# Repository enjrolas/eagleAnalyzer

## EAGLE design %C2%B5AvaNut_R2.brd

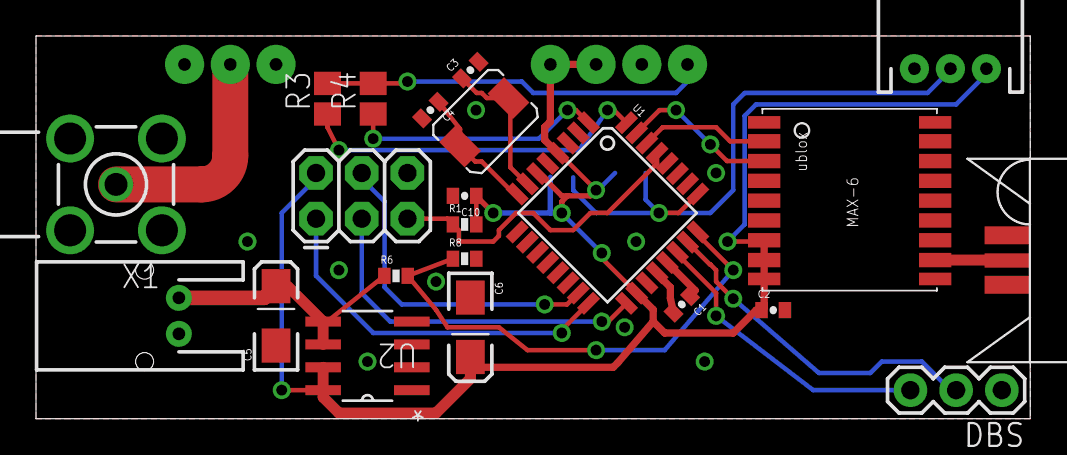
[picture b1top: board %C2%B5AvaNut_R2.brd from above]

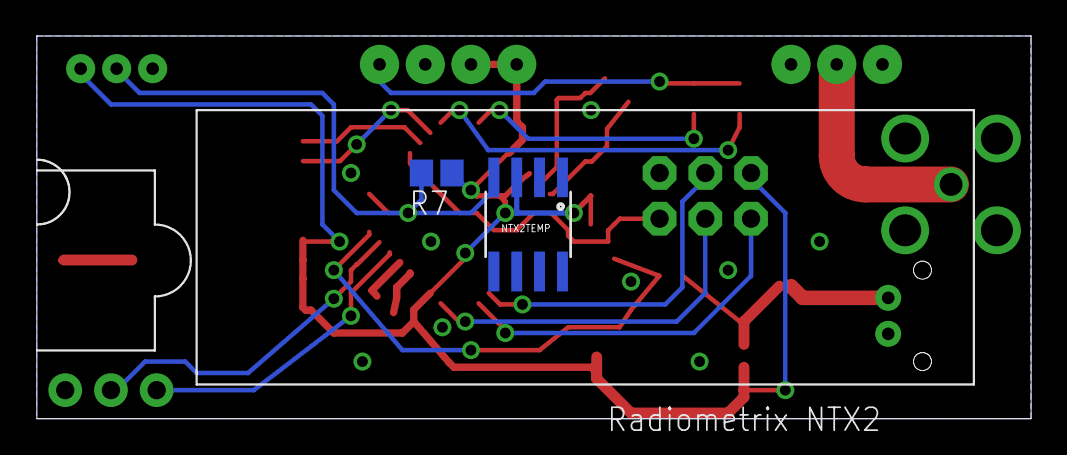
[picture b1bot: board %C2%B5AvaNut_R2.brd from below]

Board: 2 copper layers, 55.2 x 21.3 mm, 25 parts (3 on the bottom side), 21 nets.

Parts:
C1, C2, C10: 0.1uF; 0402-CAP
C3, C4: 18pF; 0402-CAP
C5: EIA3216-KIT
C6: 4.7uF; EIA3216-KIT
DBS: 1X03
FUCKINGANNOYING: AVR_SPI_PRG_6PTH; 2X3
JP6: JST-3-PTH
NTX2TEMP: DS1821; DS18B20_SOIC
R1, R8: 10k; 0402-RES
R3: 47K; R0805
R4: 39k; R0805
R6: 100k; 0402-RES
R7: 4k7; R0805
U1: ATMEGA328; TQFP32-08
U2: TPS76633D; SOIC127P600X175-8N
U$1: UBLOX_MAX-6
U$2: ABRACON_ABM3_CRYSTAL
U$3: SARANTEL-SR1202
U$4: NTX2
U$6: M02-JST-PTH
X1: BU-SMA-H

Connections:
AREF: C1.2, U1.20
GND: C1.1, C2.2, C3.2, C4.2, C5.C, C6.C, C10.2, DBS.1, FUCKINGANNOYING.6, JP6.1, NTX2TEMP.GND, R8.2, U1.3, U1.5, U1.21, U2.3, U2.4, U$1.1_GND, U$1.6_V_BCKP, U$1.10_GND, U$1.12_GND, U$3.GND1, U$3.GND2, U$4.0V, U$4.RFGND, U$4.RFGND2, U$6.1, X1.2, X1.3, X1.4, X1.5
MISO: FUCKINGANNOYING.1, U1.16
MOSI: FUCKINGANNOYING.4, U1.15
unnamed: U$4.RFOUT, X1.1
unnamed: R3.2, R4.2, U$4.TXD
unnamed: U$1.11_RF_IN, U$3.FEED
unnamed: C3.1, U1.7, U$2.P$2
unnamed: C4.1, U1.8, U$2.P$1
NSS_RX: DBS.2, U1.23
NSS_TX: DBS.3, U1.22
RADIO_MARK: R3.1, U1.32
RADIO_SPACE: R4.1, U1.1
RESET: FUCKINGANNOYING.5, R1.1, U1.29
SCK: FUCKINGANNOYING.3, U1.17
TEMPSENSORS: JP6.2, NTX2TEMP.DQ, R7.2, U1.25
UBLOX_RXD: U1.31, U$1.3_RXD1
UBLOX_TXD: U1.30, U$1.2_TXD1
VBATT: C5.A, R6.1, U2.5, U2.6, U$6.2
VBATTADC: R6.2, R8.1, U1.24
VCC: C2.1, C6.A, C10.1, FUCKINGANNOYING.2, JP6.3, NTX2TEMP.VCC, R1.2, R7.1, U1.4, U1.6, U1.18, U2.7, U2.8, U$1.7_VCC_IO, U$1.8_VCC, U$1.9_V_RESET, U$4.EN, U$4.VCC

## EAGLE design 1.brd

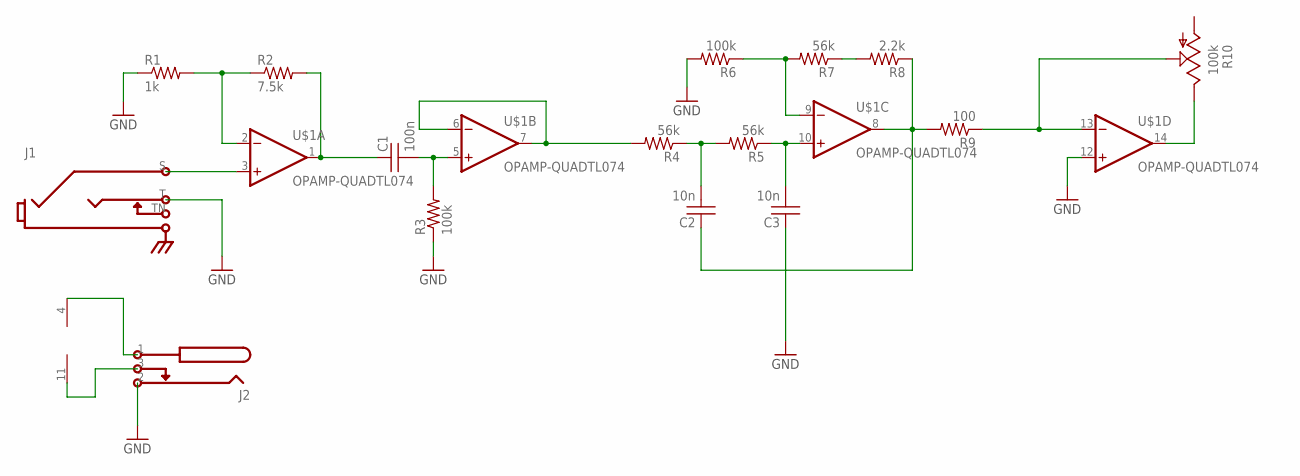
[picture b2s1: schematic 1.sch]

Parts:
C1: 100n; BOX-2.5MM-7.2MM
C2, C3: 10n; BOX-2.5MM-7.2MM
J1: MONOSW1GND; NEUTRIK-NRJ4HM-1
J2: BOSS-SWITCHING; KOBICONN-163-5010-E
R1: 1k; 0.25W-0.4IN-CARBONCOMP
R2: 7.5k; 0.25W-0.4IN-CARBONCOMP
R3, R6: 100k; 0.25W-0.4IN-CARBONCOMP
R4, R5, R7: 56k; 0.25W-0.4IN-CARBONCOMP
R8: 2.2k; 0.25W-0.4IN-CARBONCOMP
R9: 100; 0.25W-0.4IN-CARBONCOMP
R10: 100k; POT-SIDE-16MM-BITECH-P160KN
U$1: OPAMP-QUADTL074; DIP14

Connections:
0: C3.P$1 (1), J1.T, J2.2 (VCC), R1.1, R3.1, R6.2, U$1.12 (IN+)
unnamed: R1.2, R2.1, U$1.2 (IN-)
unnamed: C1.P$1 (1), R2.2, U$1.1 (OUT)
unnamed: C1.P$2 (2), R3.2, U$1.5 (IN+)
unnamed: R4.2, U$1.6 (IN-), U$1.7 (OUT)
unnamed: C2.P$2 (2), R4.1, R5.2
unnamed: C3.P$2 (2), R5.1, U$1.10 (IN+)
unnamed: R10.P$3 (3), U$1.14 (OUT)
unnamed: R6.1, R7.2, U$1.9 (IN-)
unnamed: R7.1, R8.2
unnamed: J1.S, U$1.3 (IN+)
unnamed: R9.1, R10.P$2 (2), U$1.13 (IN-)
unnamed: J2.1 (GND), U$1.4 (VCC)
unnamed: J2.3 (SW), U$1.11 (VEE)
unnamed: C2.P$1 (1), R8.1, R9.2, U$1.8 (OUT)

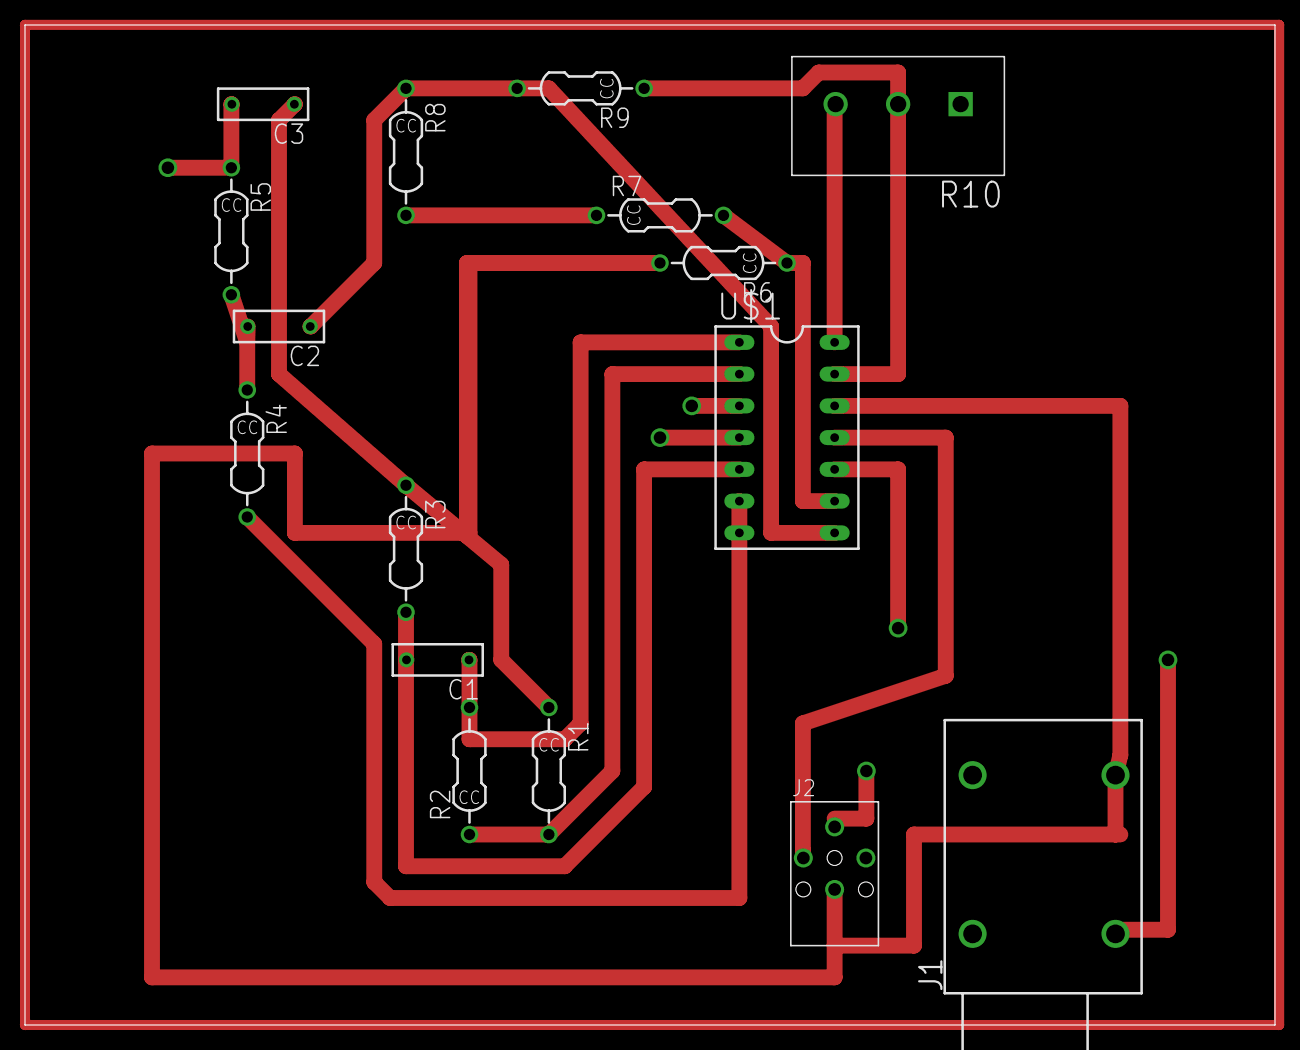
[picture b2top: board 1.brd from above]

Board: 2 copper layers, 100.0 x 80.0 mm, 16 parts (0 on the bottom side), 15 nets.

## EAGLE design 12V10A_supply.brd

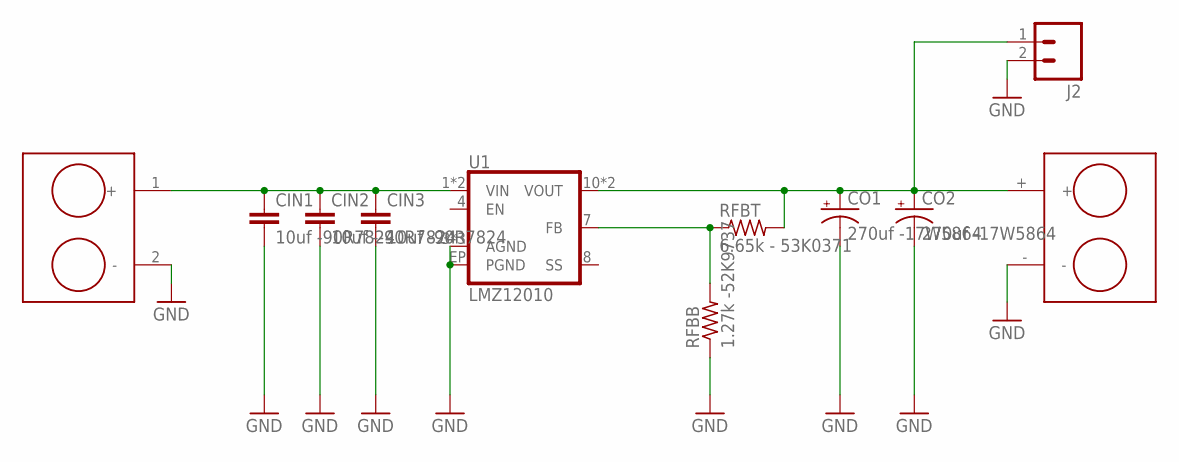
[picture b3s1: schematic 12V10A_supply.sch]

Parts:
CIN1, CIN3: 10uf -90R7824; C1210
CIN2: 10uf --90R7824; C1210
CO1, CO2: 270uf -17W5864; JC0CAP
J1: 5569-02A2MS-225; 0050362375
J2: M02PTH; 1X02
J3: MC24356; 2PINTERMINAL
RFBB: 1.27k -52K9737; M0805
RFBT: 6.65k - 53K0371; M0805
U1: LMZ12010; TO-PMOD-11

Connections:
GND: CIN1.2, CIN2.2, CIN3.2, CO1.-, CO2.-, J1.2 (-), J2.2, J3.-, RFBB.1, U1.3 (AGND), U1.5 (AGND), U1.6 (AGND), U1.EP (PGND)
unnamed: RFBB.2, RFBT.1, U1.7 (FB)
VIN: CIN1.1, CIN2.1, CIN3.1, J1.1 (+), U1.1 (VIN), U1.2 (VIN)
VOUT: CO1.+, CO2.+, J2.1, J3.+, RFBT.2, U1.10 (VOUT), U1.11 (VOUT)

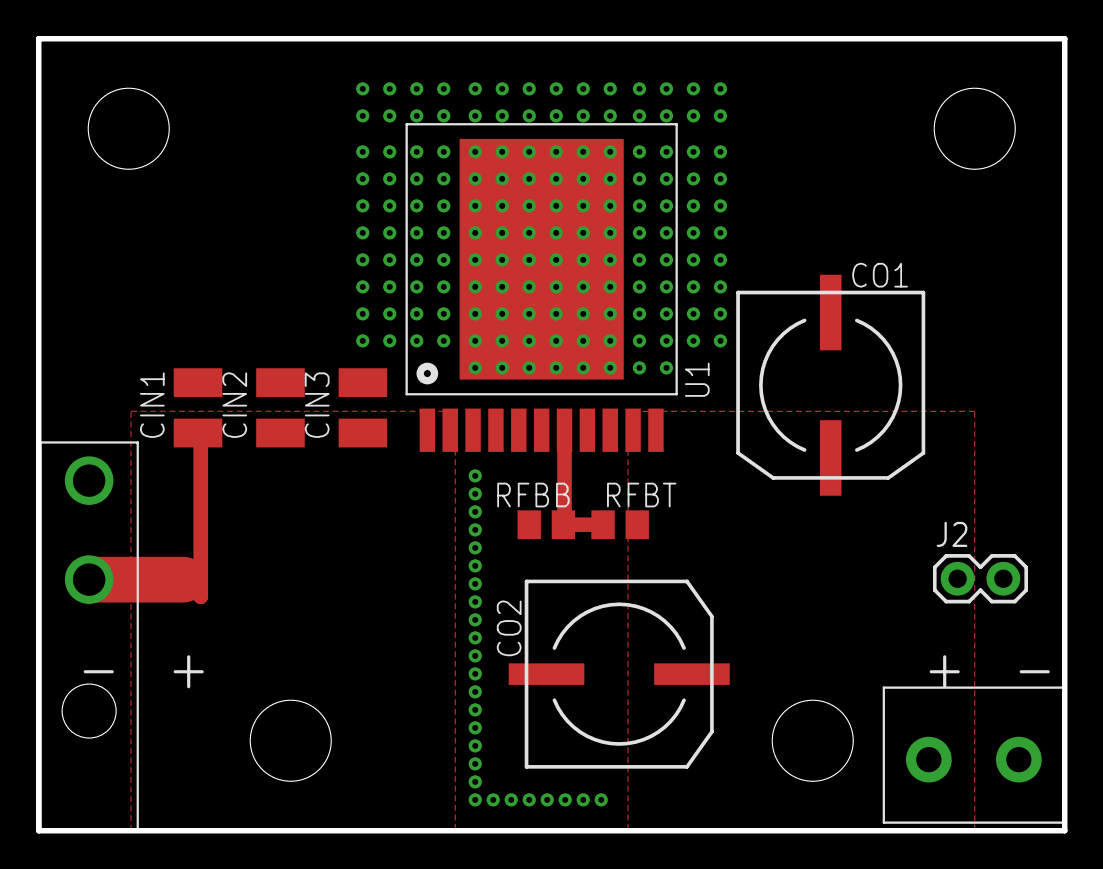
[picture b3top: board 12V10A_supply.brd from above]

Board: 2 copper layers, 57.0 x 44.0 mm, 11 parts (0 on the bottom side), 4 nets.

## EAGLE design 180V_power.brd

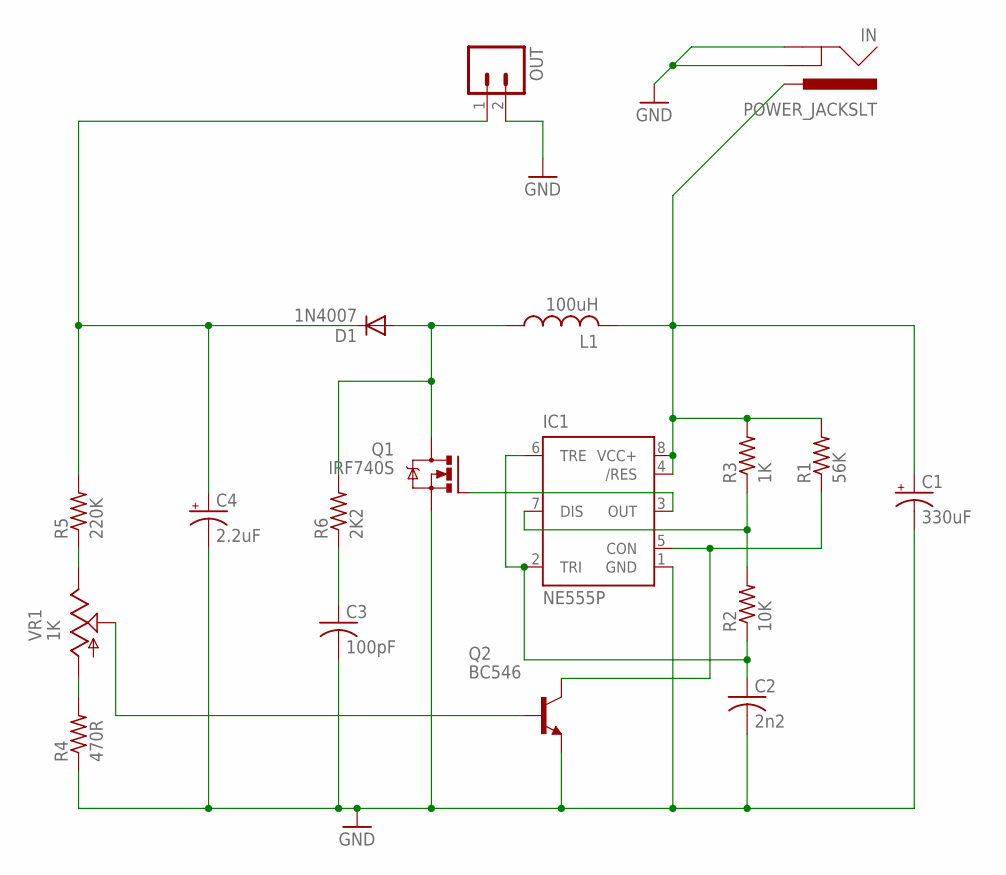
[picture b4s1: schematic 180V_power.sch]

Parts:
C1: 330uF; E5-10,5
C2: 2n2; C1206K
C3: 100pF; C1206K
C4: 2.2uF; E3,5-8
D1: 1N4007; SMA-DIODE
IC1: NE555P; DIL08
IN: POWER_JACKSLT; POWER_JACK_SLOT
L1: 100uH; TFI0307
OUT: M023.5MM; SCREWTERMINAL-3.5MM-2
Q1: IRF740S; TO263
Q2: BC546; TO92-EBC
R1: 56K; R1206
R2: 10K; R1206
R3: 1K; R1206
R4: 470R; 0207/10
R5: 220K; 0207/10
R6: 2K2; R1206
VR1: 1K; CA6V

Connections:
GND: C1.-, C2.2, C3.2, C4.-, IC1.1 (GND), IN.GND@1 (GNDBREAK), IN.GND@2 (GND), OUT.2, Q1.2 (S), Q2.E, R4.1
unnamed: IC1.3 (OUT), Q1.1 (G)
unnamed: C3.1, R6.1
unnamed: IC1.5 (CON), Q2.C, R1.1
unnamed: IC1.7 (DIS), R2.2, R3.1
unnamed: C2.1, IC1.2 (TRI), IC1.6 (TRE), R2.1
unnamed: D1.A, L1.1, Q1.3 (D), R6.2
unnamed: C4.+, D1.C, OUT.1, R5.2
unnamed: R5.1, VR1.E
unnamed: R4.2, VR1.A
unnamed: Q2.B, VR1.S
unnamed: C1.+, IC1.4 (/RES), IC1.8 (VCC+), IN.PWR, L1.2, R1.2, R3.2

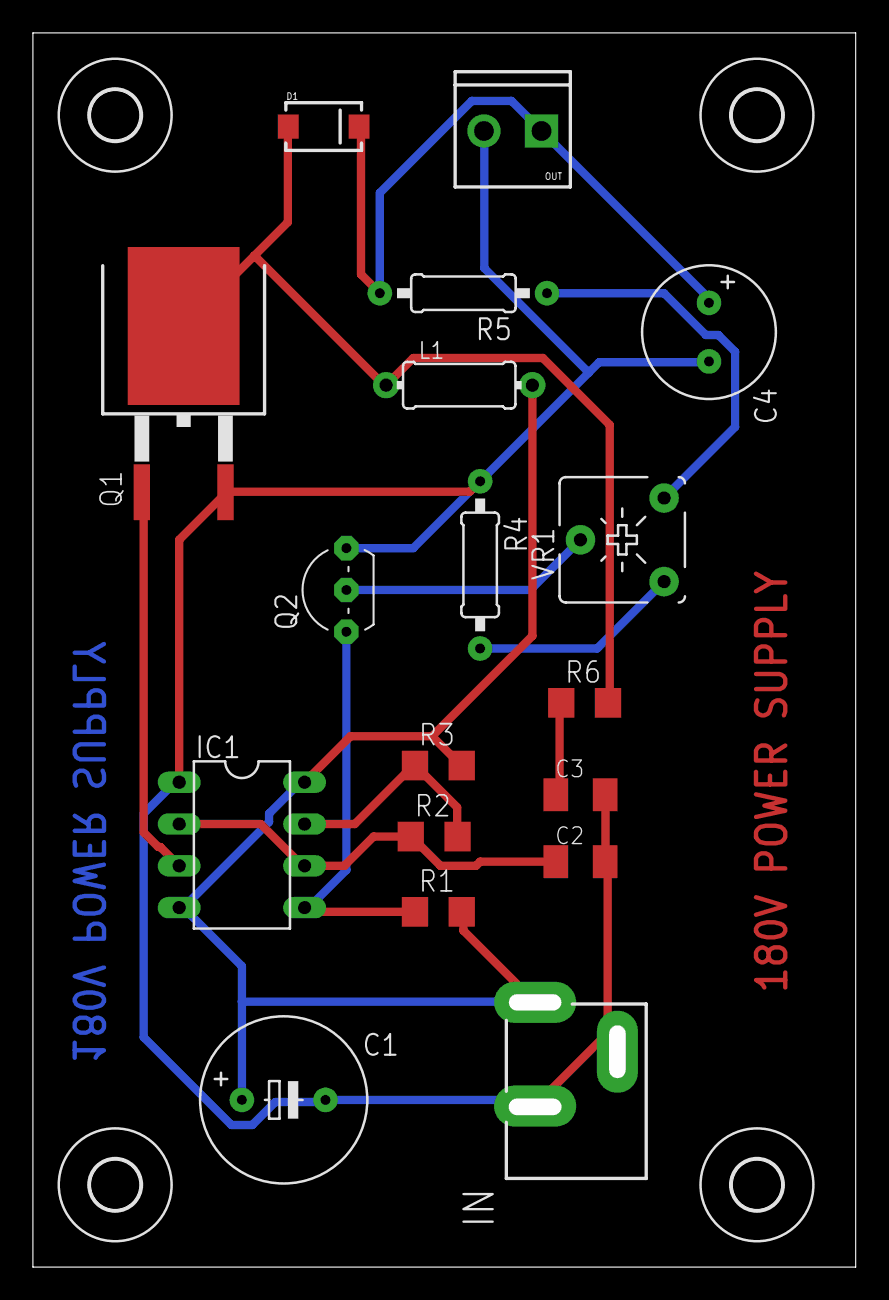
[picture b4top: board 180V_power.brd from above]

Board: 2 copper layers, 50.0 x 75.0 mm, 22 parts (0 on the bottom side), 12 nets.

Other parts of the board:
U$1, U$2, U$3, U$4: 3,0

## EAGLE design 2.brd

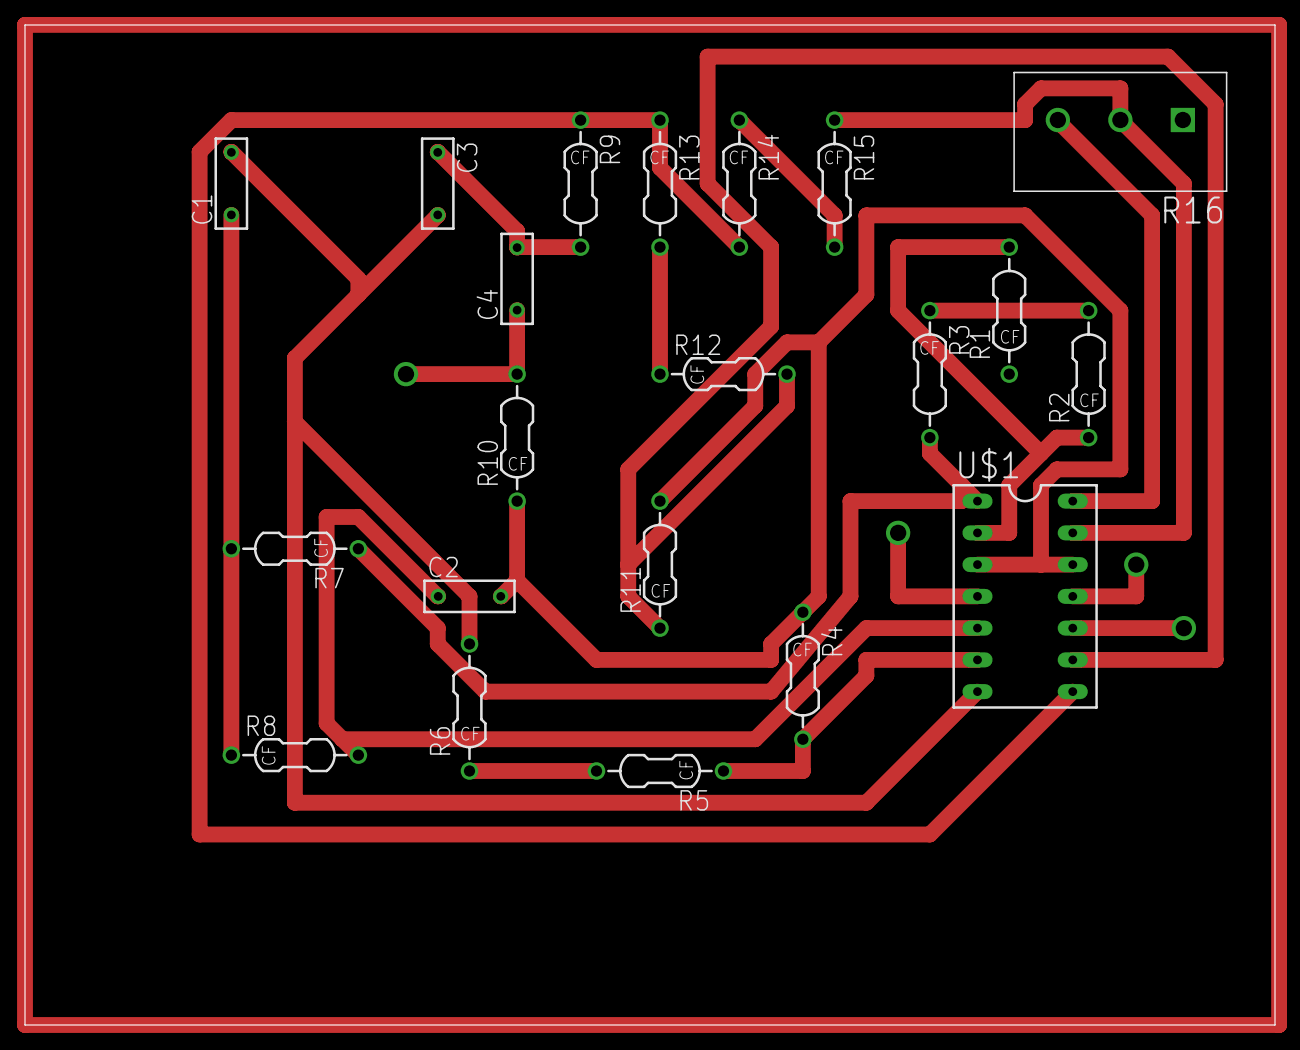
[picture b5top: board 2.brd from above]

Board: 2 copper layers, 100.0 x 80.0 mm, 21 parts (0 on the bottom side), 17 nets.

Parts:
C1, C2, C3, C4: 10n; BOX-2.5MM-7.2MM
R1, R4, R11, R15: 100k; 0.25W-0.4IN-CARBONFILM
R2, R5, R9, R10, R12: 56k; 0.25W-0.4IN-CARBONFILM
R3: 6.8k; 0.25W-0.4IN-CARBONFILM
R6, R13: 2.2k; 0.25W-0.4IN-CARBONFILM
R7, R8: 5.6k; 0.25W-0.4IN-CARBONFILM
R14: 100; 0.25W-0.4IN-CARBONFILM
R16: 100k; POT-SIDE-16MM-BITECH-P160KN
U$1: OPAMP-QUADTL074; DIP14

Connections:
0: C2.P$2, R4.1, R10.1, R11.2, U$1.3, U$1.12
unnamed: R1.2, R2.1, U$1.2
unnamed: R2.2, R3.1
unnamed: R3.2, R7.1, U$1.1
unnamed: C1.P$1, R7.2, R8.1
unnamed: C2.P$1, R8.2, U$1.5
unnamed: R4.2, R5.1, U$1.6
unnamed: R5.2, R6.1
unnamed: R16.P$3, U$1.14
unnamed: C3.P$1, C4.P$2, R9.2
unnamed: R11.1, R12.2, U$1.9
unnamed: R12.1, R13.2
unnamed: C4.P$1, R10.2, U$1.10
unnamed: R14.1, R15.2
unnamed: R15.1, R16.P$2, U$1.13
unnamed: C1.P$2, C3.P$2, R6.2, U$1.7
unnamed: R9.1, R13.1, R14.2, U$1.8

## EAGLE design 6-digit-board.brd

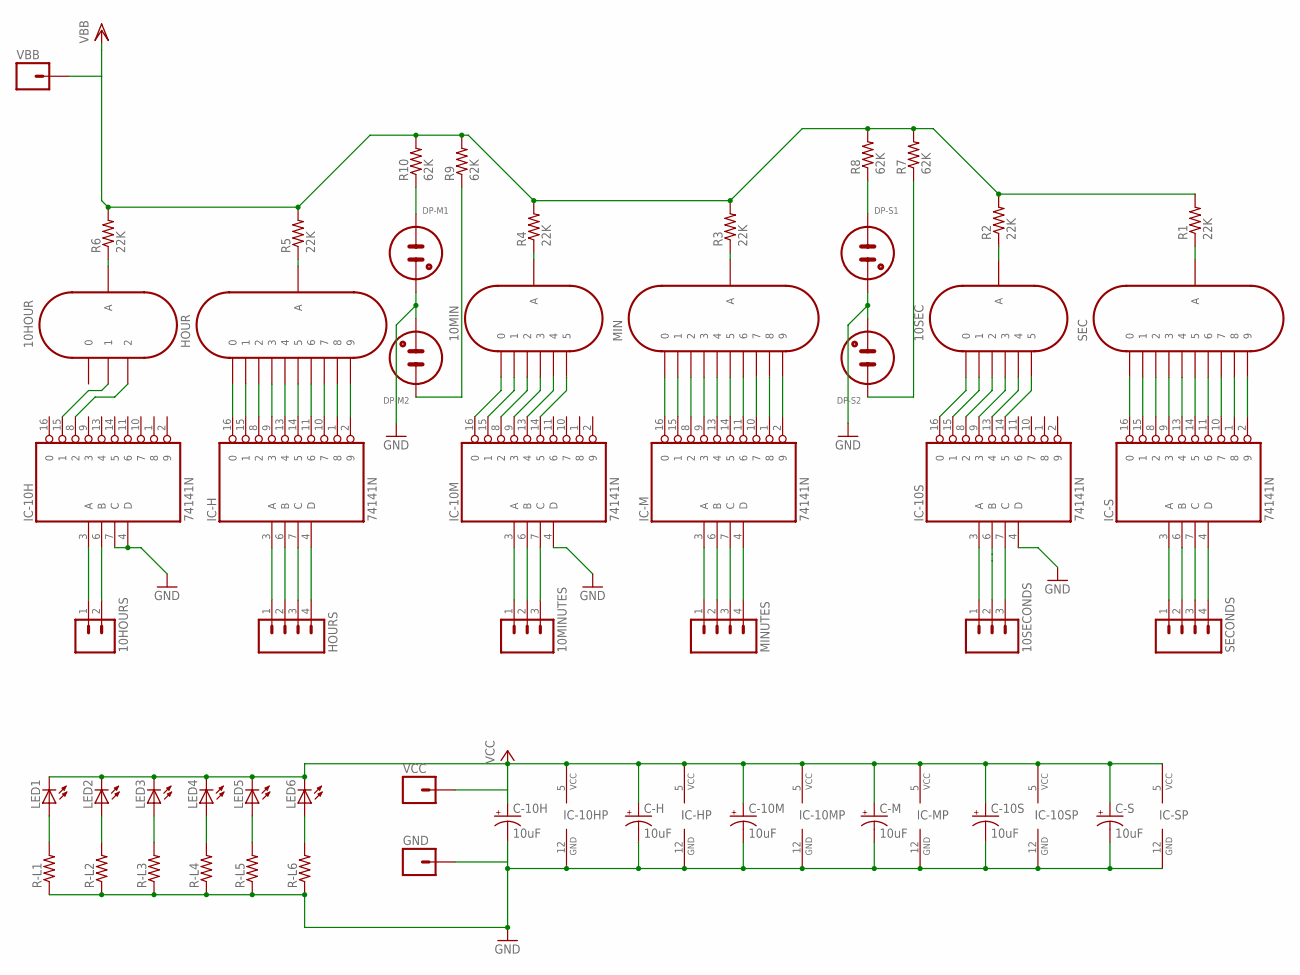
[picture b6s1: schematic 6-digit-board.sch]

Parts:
10HOUR: IN-12_2DIGIT
10HOURS: M02PTH3; 1X02_LONGPADS
10MIN, 10SEC: IN-12_6DIGIT
10MINUTES, 10SECONDS: M03LONGPADS; 1X03_LONGPADS
C-10H, C-10M, C-10S: 10uF; B/3528-21R
C-H: 10uF; B/3528-21R
C-M: 10uF; B/3528-21R
C-S: 10uF; B/3528-21R
DP-M1, DP-M2: INS-1
DP-S1, DP-S2: INS-1
GND: M01PTH; 1X01
HOUR: IN-12A-NO_DP; IN-12_NO-DP
HOURS: M04LONGPADS; 1X04_LONGPADS
IC-10H, IC-10M, IC-10S: 74141N; DIL16
IC-H: 74141N; DIL16
IC-M: 74141N; DIL16
IC-S: 74141N; DIL16
LED1, LED2, LED3, LED4, LED5, LED6: LED1210
MIN: IN-12A-NO_DP; IN-12_NO-DP
MINUTES: M04LONGPADS; 1X04_LONGPADS
R1, R2, R3, R4, R5, R6: 22K; 0207/10
R7, R8, R9, R10: 62K; 0207/10
R-L1, R-L2, R-L3, R-L4, R-L5, R-L6: RESISTORR1206; R1206
SEC: IN-12A-NO_DP; IN-12_NO-DP
SECONDS: M04LONGPADS; 1X04_LONGPADS
VBB: M01PTH; 1X01
VCC: M01PTH; 1X01

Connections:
GND: C-10H.-, C-10M.-, C-10S.-, C-H.-, C-M.-, C-S.-, DP-M1.K, DP-M2.K, DP-S1.K, DP-S2.K, GND.1, IC-10H.4 (D), IC-10H.7 (C), IC-10H.12 (GND), IC-10M.4 (D), IC-10M.12 (GND), IC-10S.4 (D), IC-10S.12 (GND), IC-H.12 (GND), IC-M.12 (GND), IC-S.12 (GND), R-L1.1, R-L2.1, R-L3.1, R-L4.1, R-L5.1, R-L6.1
unnamed: 10HOUR.A, R6.1
unnamed: HOUR.A, R5.1
unnamed: 10MIN.A, R4.1
unnamed: MIN.A, R3.1
unnamed: 10SEC.A, R2.1
unnamed: R1.1, SEC.A
unnamed: HOURS.1, IC-H.3 (A)
unnamed: HOURS.2, IC-H.6 (B)
unnamed: DP-M1.A, R10.1
unnamed: DP-M2.A, R9.1
unnamed: DP-S1.A, R8.1
unnamed: DP-S2.A, R7.1
unnamed: HOUR.0, IC-H.16 (0)
unnamed: HOUR.1, IC-H.15 (1)
unnamed: HOUR.2, IC-H.8 (2)
unnamed: HOUR.3, IC-H.9 (3)
unnamed: HOUR.4, IC-H.13 (4)
unnamed: HOUR.5, IC-H.14 (5)
unnamed: HOUR.6, IC-H.11 (6)
unnamed: HOUR.7, IC-H.10 (7)
unnamed: HOUR.8, IC-H.1 (8)
unnamed: HOUR.9, IC-H.2 (9)
unnamed: 10HOUR.1, IC-10H.15 (1)
unnamed: 10HOUR.2, IC-10H.8 (2)
unnamed: 10MIN.0, IC-10M.16 (0)
unnamed: 10MIN.1, IC-10M.15 (1)
unnamed: 10MIN.2, IC-10M.8 (2)
unnamed: 10MIN.3, IC-10M.9 (3)
unnamed: 10MIN.4, IC-10M.13 (4)
unnamed: 10MIN.5, IC-10M.14 (5)
unnamed: IC-M.16 (0), MIN.0
unnamed: IC-M.15 (1), MIN.1
unnamed: IC-M.8 (2), MIN.2
unnamed: IC-M.9 (3), MIN.3
unnamed: IC-M.13 (4), MIN.4
unnamed: IC-M.14 (5), MIN.5
unnamed: IC-M.11 (6), MIN.6
unnamed: IC-M.10 (7), MIN.7
unnamed: IC-M.1 (8), MIN.8
unnamed: IC-M.2 (9), MIN.9
unnamed: 10SEC.0, IC-10S.16 (0)
unnamed: 10SEC.1, IC-10S.15 (1)
unnamed: 10SEC.2, IC-10S.8 (2)
unnamed: 10SEC.3, IC-10S.9 (3)
unnamed: 10SEC.4, IC-10S.13 (4)
unnamed: 10SEC.5, IC-10S.14 (5)
unnamed: IC-S.16 (0), SEC.0
unnamed: IC-S.15 (1), SEC.1
unnamed: IC-S.8 (2), SEC.2
unnamed: IC-S.9 (3), SEC.3
unnamed: IC-S.13 (4), SEC.4
unnamed: IC-S.14 (5), SEC.5
unnamed: IC-S.11 (6), SEC.6
unnamed: IC-S.10 (7), SEC.7
unnamed: IC-S.1 (8), SEC.8
unnamed: IC-S.2 (9), SEC.9
unnamed: HOURS.3, IC-H.7 (C)
unnamed: HOURS.4, IC-H.4 (D)
unnamed: IC-S.3 (A), SECONDS.1
unnamed: IC-S.6 (B), SECONDS.2
unnamed: IC-S.7 (C), SECONDS.3
unnamed: IC-S.4 (D), SECONDS.4
unnamed: IC-M.3 (A), MINUTES.1
unnamed: IC-M.6 (B), MINUTES.2
unnamed: IC-M.7 (C), MINUTES.3
unnamed: IC-M.4 (D), MINUTES.4
unnamed: 10SECONDS.1, IC-10S.3 (A)
unnamed: 10SECONDS.2, IC-10S.6 (B)
unnamed: 10SECONDS.3, IC-10S.7 (C)
unnamed: 10MINUTES.1, IC-10M.3 (A)
unnamed: 10MINUTES.2, IC-10M.6 (B)
unnamed: 10MINUTES.3, IC-10M.7 (C)
unnamed: 10HOURS.1, IC-10H.3 (A)
unnamed: 10HOURS.2, IC-10H.6 (B)
unnamed: LED1.A, R-L1.2
unnamed: LED2.A, R-L2.2
unnamed: LED3.A, R-L3.2
unnamed: LED4.A, R-L4.2
unnamed: LED5.A, R-L5.2
unnamed: LED6.A, R-L6.2
VBB: R1.2, R2.2, R3.2, R4.2, R5.2, R6.2, R7.2, R8.2, R9.2, R10.2, VBB.1
VCC: C-10H.+, C-10M.+, C-10S.+, C-H.+, C-M.+, C-S.+, IC-10H.5 (VCC), IC-10M.5 (VCC), IC-10S.5 (VCC), IC-H.5 (VCC), IC-M.5 (VCC), IC-S.5 (VCC), LED1.C, LED2.C, LED3.C, LED4.C, LED5.C, LED6.C, VCC.1

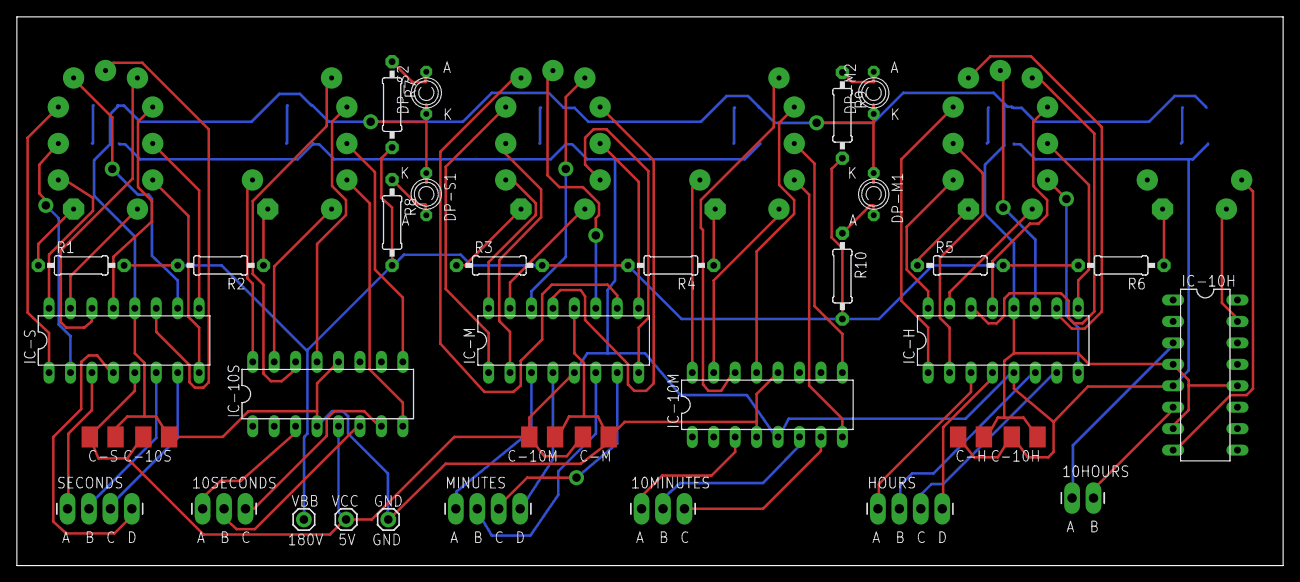
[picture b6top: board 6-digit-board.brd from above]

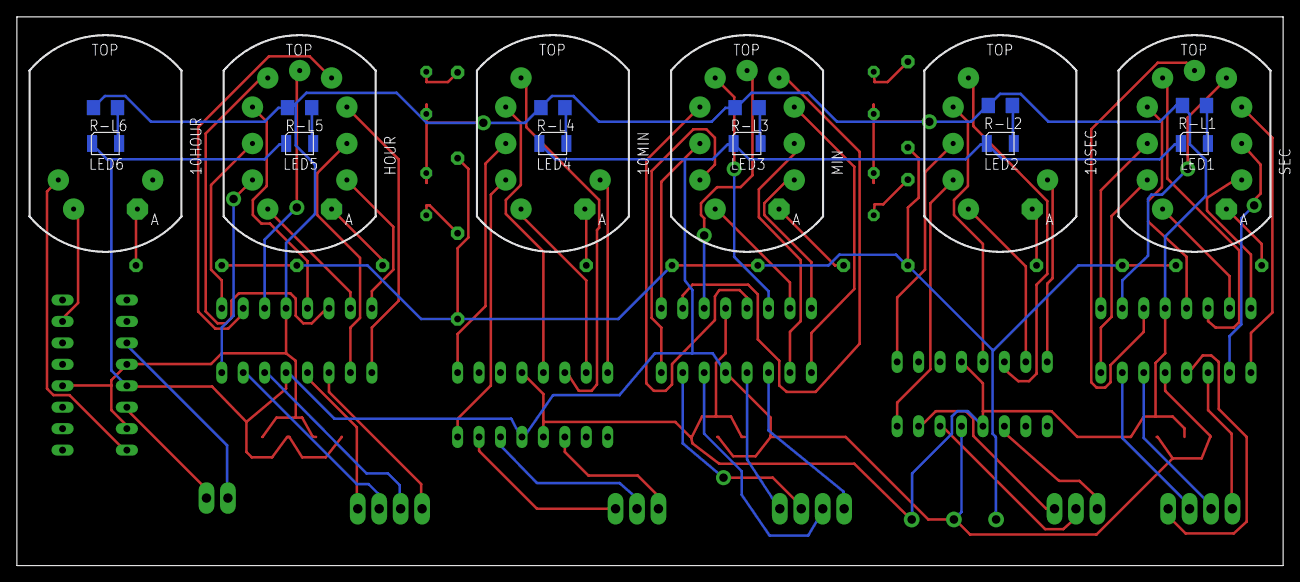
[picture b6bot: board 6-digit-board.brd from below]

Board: 2 copper layers, 150.0 x 65.0 mm, 53 parts (18 on the bottom side), 83 nets.

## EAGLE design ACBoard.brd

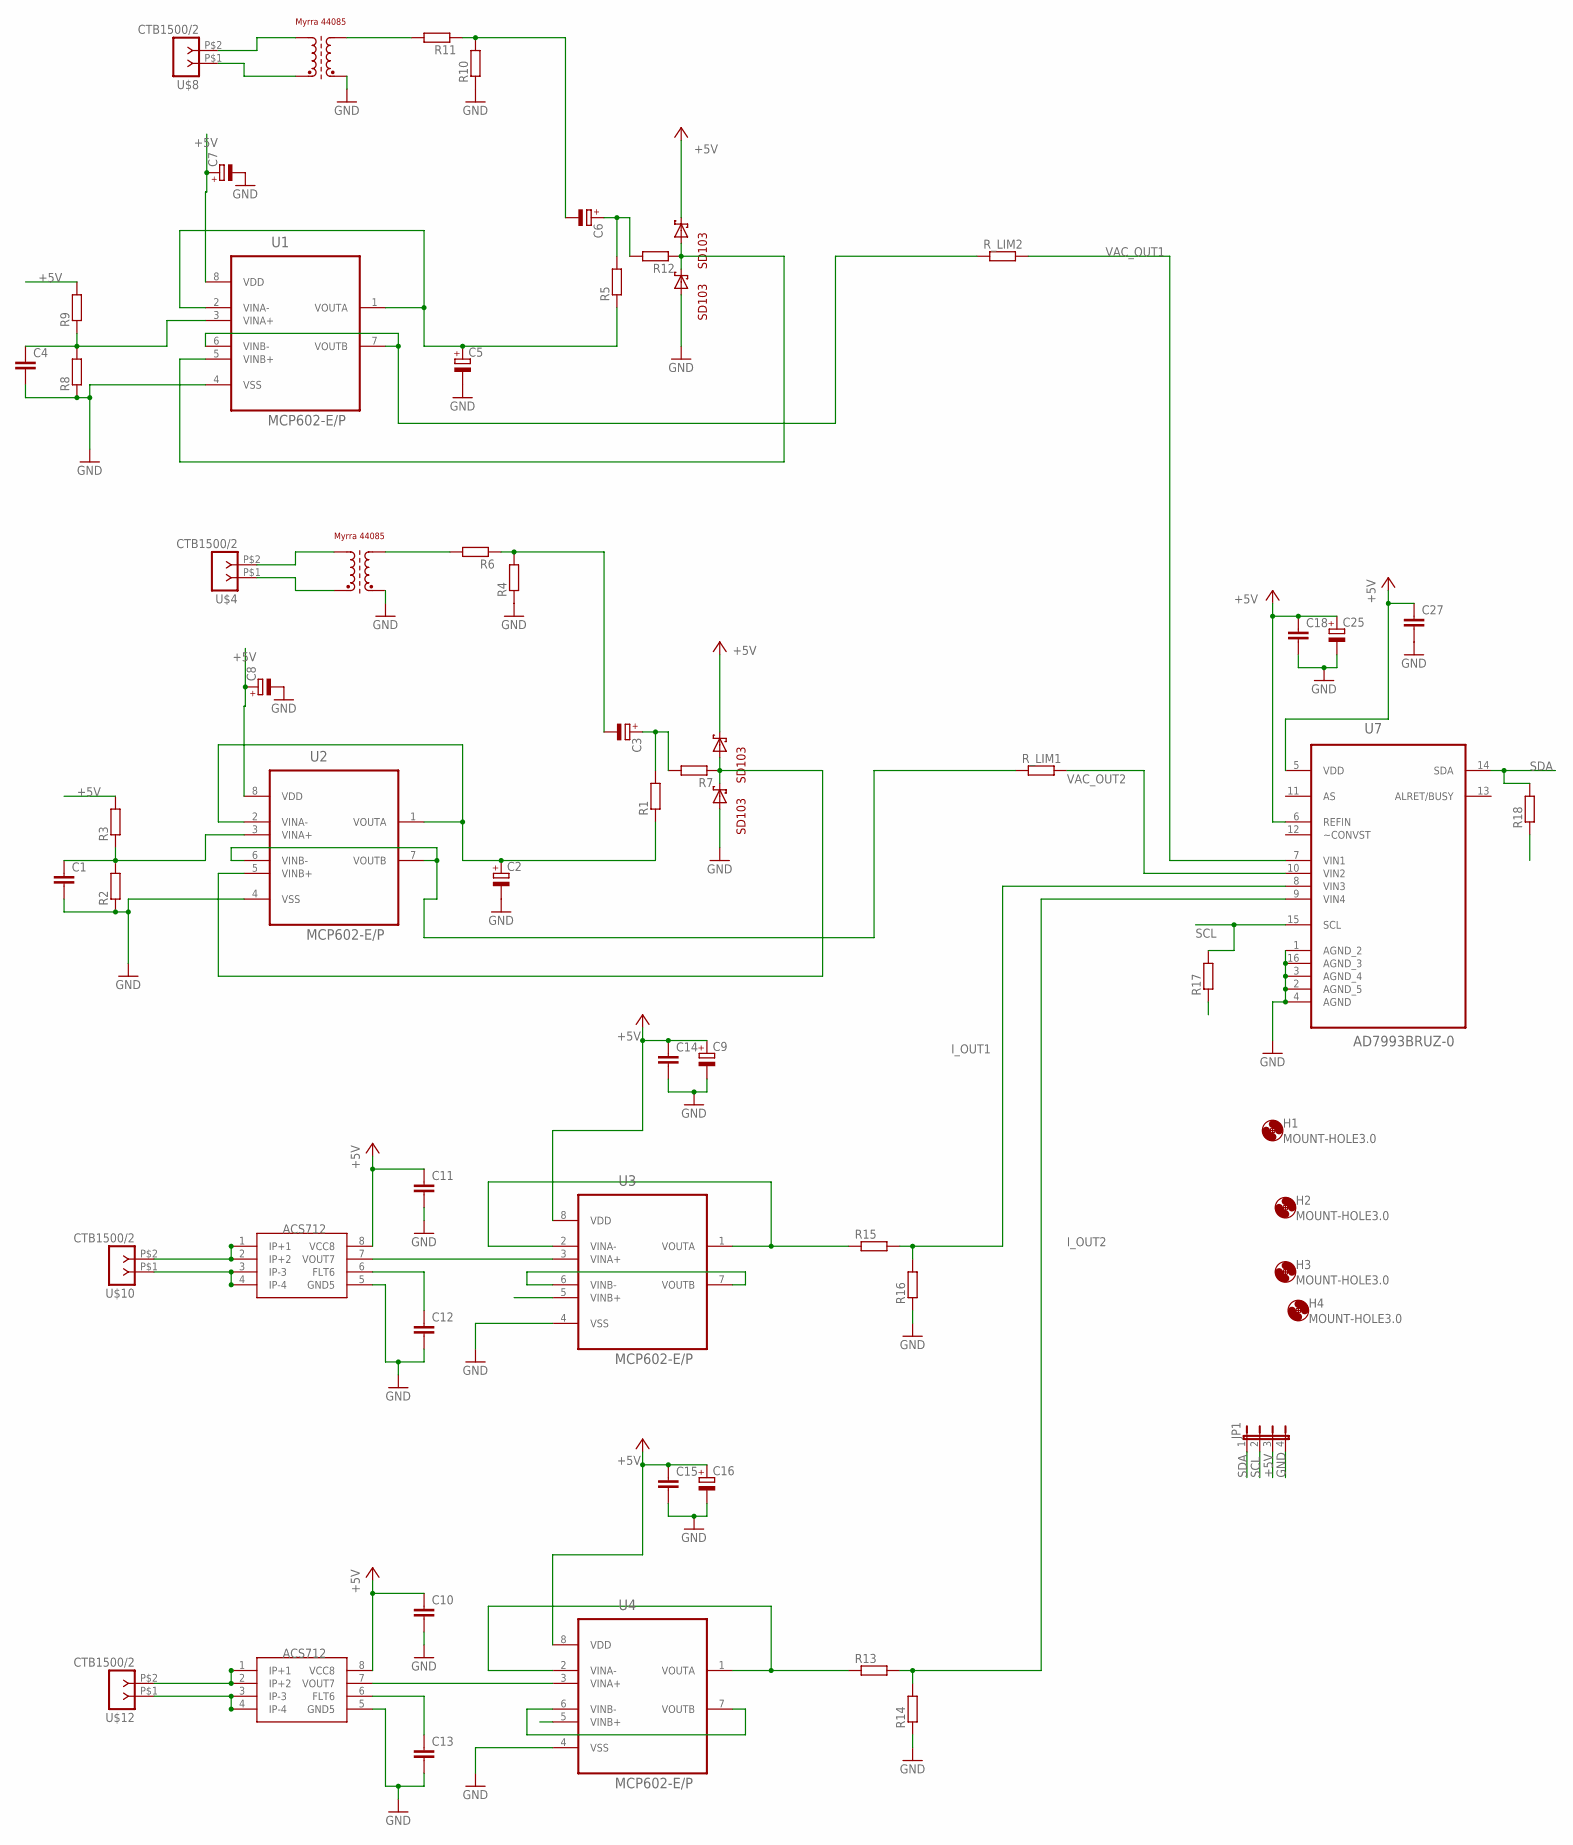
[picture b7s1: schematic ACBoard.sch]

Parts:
C1, C4: C5P; C050-030-075
C2, C3, C5, C6, C7, C8: CPOL1; E2,5-7---100UF
C9, C16, C25: CPOL-EUE2-4; E2-4
C10, C11, C12, C13, C14, C15, C18: C-EU025-024X044; C025-024X044
C27: C-EU025-025X050; C025-025X050
H1, H2, H3, H4: MOUNT-HOLE3.0; 3,0
JP1: JP4E; JP4
R1, R2, R3, R4, R5, R6, R7, R8, R9, R10, R11, R12: R; 0207/10
R13, R14, R15, R16, R17, R18: R-EU_0207/7; 0207/7
R_LIM1, R_LIM2: R; 0207/10
U1, U2, U3, U4: MCP602-E/P; DIP254P762X508-8P
U7: AD7993BRUZ-0; SOP65P640X120-16N
U$1, U$5: MYRRA_4408; 4408
U$2, U$3, U$6, U$7: SD103A; D035-10
U$4, U$8, U$10, U$12: CTB1500/2; CTB1500-2
U$9, U$11: ACS712; SO8

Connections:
+5V: C7.+, C8.+, C9.+, C10.1, C11.1, C14.1, C15.1, C16.+, C18.1, C25.+, C27.1, JP1.3, R3.2, R9.2, R17.1, R18.1, U1.8 (VDD), U2.8 (VDD), U3.8 (VDD), U4.8 (VDD), U7.5 (VDD), U7.6 (REFIN), U$2.C, U$6.C, U$9.8 (VCC8), U$11.8 (VCC8)
GND: C1.2, C2.-, C4.2, C5.-, C7.-, C8.-, C9.-, C10.2, C11.2, C12.2, C13.2, C14.2, C15.2, C16.-, C18.2, C25.-, C27.2, JP1.4, R2.1, R4.1, R8.1, R10.1, R14.1, R16.1, U1.4 (VSS), U2.4 (VSS), U3.4 (VSS), U3.5 (VINB+), U4.4 (VSS), U4.5 (VINB+), U7.1 (AGND_2), U7.2 (AGND_5), U7.3 (AGND_4), U7.4 (AGND), U7.16 (AGND_3), U$1.PIN9 (E2), U$3.A, U$5.PIN9 (E2), U$7.A, U$9.5 (GND5), U$11.5 (GND5)
IOUTOP: R15.1, U3.1 (VOUTA), U3.2 (VINA-)
IOUTOP2: R13.1, U4.1 (VOUTA), U4.2 (VINA-)
I_OUT1: R15.2, R16.2, U7.8 (VIN3)
I_OUT2: R13.2, R14.2, U7.9 (VIN4)
unnamed: R_LIM2.1, U1.6 (VINB-), U1.7 (VOUTB)
unnamed: C5.+, R5.1, U1.1 (VOUTA), U1.2 (VINA-)
unnamed: C1.1, R2.2, R3.1, U2.3 (VINA+)
unnamed: R7.1, U2.5 (VINB+), U$2.A, U$3.C
unnamed: C3.-, R4.2, R6.1
unnamed: U$9.3 (IP-3), U$9.4 (IP-4), U$10.P$1 (1)
unnamed: R6.2, U$1.PIN7 (A2)
unnamed: C12.1, U$9.6 (FLT6)
unnamed: C3.+, R1.2, R7.2
unnamed: C4.1, R8.2, R9.1, U1.3 (VINA+)
unnamed: U$5.PIN5 (A1), U$8.P$2 (2)
unnamed: R12.1, U1.5 (VINB+), U$6.A, U$7.C
unnamed: C2.+, R1.1, U2.1 (VOUTA), U2.2 (VINA-)
unnamed: R_LIM1.1, U2.6 (VINB-), U2.7 (VOUTB)
unnamed: U$5.PIN1 (E1), U$8.P$1 (1)
unnamed: U3.3 (VINA+), U$9.7 (VOUT7)
unnamed: C6.-, R10.2, R11.1
unnamed: R11.2, U$5.PIN7 (A2)
unnamed: U$1.PIN5 (A1), U$4.P$2 (2)
unnamed: U$9.1 (IP+1), U$9.2 (IP+2), U$10.P$2 (2)
unnamed: C6.+, R5.2, R12.2
unnamed: U$11.3 (IP-3), U$11.4 (IP-4), U$12.P$1 (1)
unnamed: C13.1, U$11.6 (FLT6)
unnamed: U4.3 (VINA+), U$11.7 (VOUT7)
unnamed: U$11.1 (IP+1), U$11.2 (IP+2), U$12.P$2 (2)
unnamed: U$1.PIN1 (E1), U$4.P$1 (1)
unnamed: U4.6 (VINB-), U4.7 (VOUTB)
unnamed: U3.6 (VINB-), U3.7 (VOUTB)
SCL: JP1.2, R17.2, U7.15 (SCL)
SDA: JP1.1, R18.2, U7.14 (SDA)
VAC_OUT1: R_LIM2.2, U7.7 (VIN1)
VAC_OUT2: R_LIM1.2, U7.10 (VIN2)

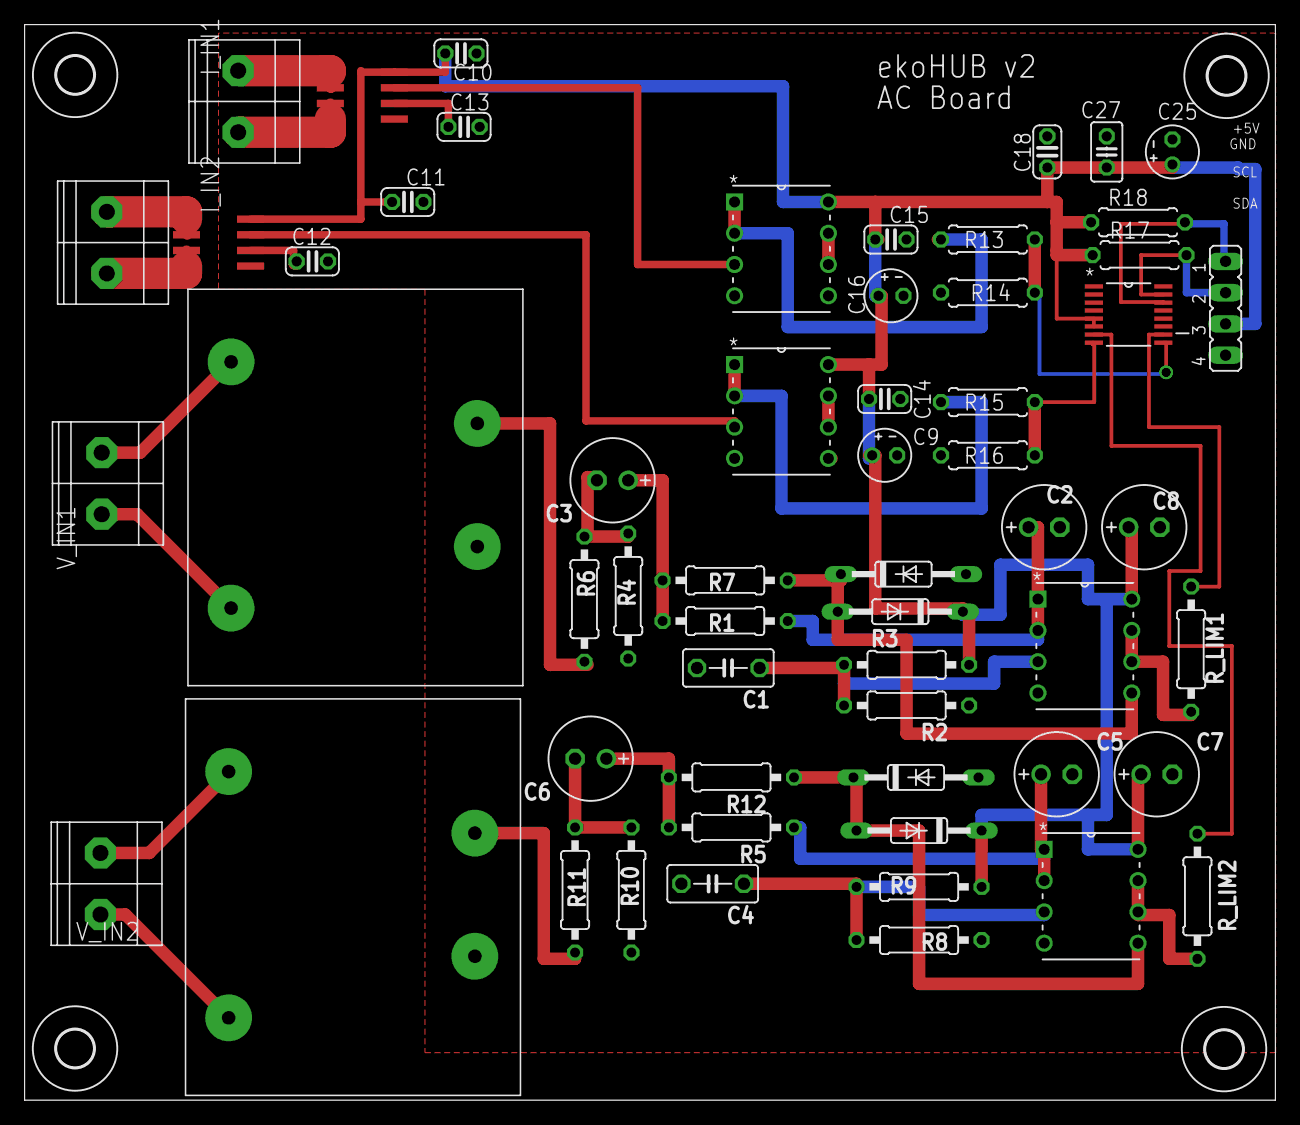
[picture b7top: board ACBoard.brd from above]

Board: 2 copper layers, 101.6 x 87.4 mm, 61 parts (0 on the bottom side), 38 nets.

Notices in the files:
parts and their libraries:
SparkFun-Connectors: Licensing: CC v3.0 Share-Alike You are welcome to use this library for commercial purposes.
